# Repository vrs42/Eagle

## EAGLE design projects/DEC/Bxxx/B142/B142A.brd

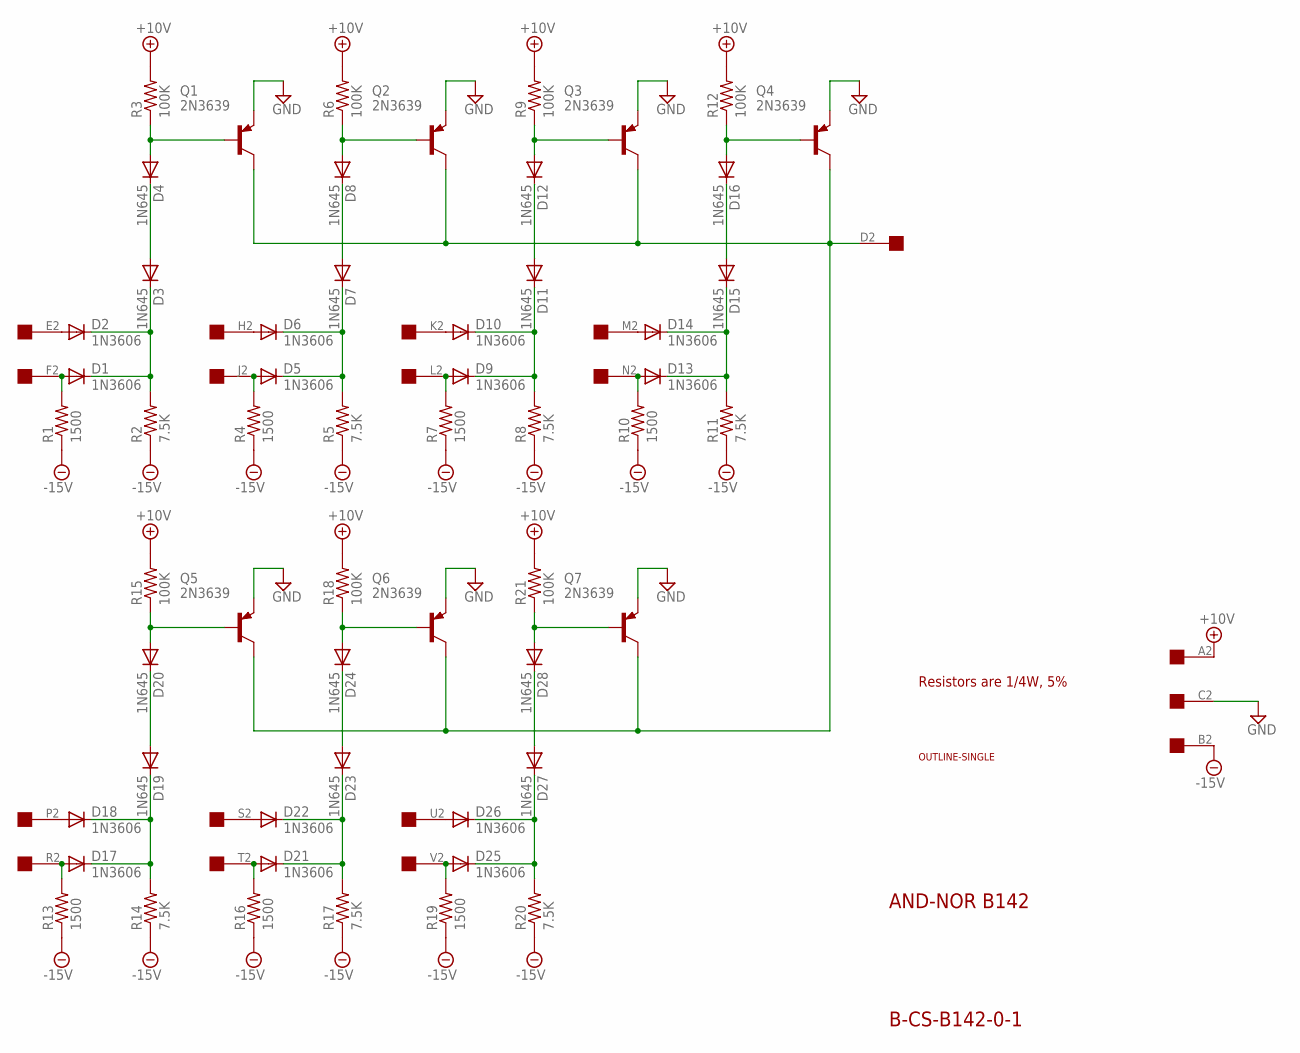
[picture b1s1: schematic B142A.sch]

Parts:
D1, D2, D5, D6, D9, D10, D13, D14, D17, D18, D21, D22, D25, D26: 1N3606; DO35-10
D3, D4, D7, D8, D11, D12, D15, D16, D19, D20, D23, D24, D27, D28: 1N645; DO35-10
Q1, Q2, Q3, Q4, Q5, Q6, Q7: 2N3639; TO39
R1, R4, R7, R10, R13, R16, R19: 1500; 0207/10
R2, R5, R8, R11, R14, R17, R20: 7.5K; 0207/10
R3, R6, R9, R12, R15, R18, R21: 100K; 0207/10
U$1: OUTLINE-SINGLE; SINGLE
U$2: EDGE-1; EDGE-CON1

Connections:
+10V: R3.2, R6.2, R9.2, R12.2, R15.2, R18.2, R21.2, U$2.A2
-15V: R1.1, R2.1, R4.1, R5.1, R7.1, R8.1, R10.1, R11.1, R13.1, R14.1, R16.1, R17.1, R19.1, R20.1, U$2.B2
GND: Q1.1 (E), Q2.1 (E), Q3.1 (E), Q4.1 (E), Q5.1 (E), Q6.1 (E), Q7.1 (E), U$2.C2
unnamed: D22.A, U$2.S2
unnamed: D4.A, Q1.2 (B), R3.1
unnamed: D3.A, D4.C
unnamed: Q1.3 (C), Q2.3 (C), Q3.3 (C), Q4.3 (C), Q5.3 (C), Q6.3 (C), Q7.3 (C), U$2.D2
unnamed: D5.A, R4.2, U$2.J2
unnamed: D12.A, Q3.2 (B), R9.1
unnamed: D10.A, U$2.K2
unnamed: D26.A, U$2.U2
unnamed: D14.A, U$2.M2
unnamed: D9.A, R7.2, U$2.L2
unnamed: D8.A, Q2.2 (B), R6.1
unnamed: D18.A, U$2.P2
unnamed: D11.A, D12.C
unnamed: D25.A, R19.2, U$2.V2
unnamed: D16.A, Q4.2 (B), R12.1
unnamed: D25.C, D26.C, D27.C, R20.2
unnamed: D15.A, D16.C
unnamed: D1.C, D2.C, D3.C, R2.2
unnamed: D5.C, D6.C, D7.C, R5.2
unnamed: D2.A, U$2.E2
unnamed: D1.A, R1.2, U$2.F2
unnamed: D7.A, D8.C
unnamed: D6.A, U$2.H2
unnamed: D13.C, D14.C, D15.C, R11.2
unnamed: D17.C, D18.C, D19.C, R14.2
unnamed: D13.A, R10.2, U$2.N2
unnamed: D20.A, Q5.2 (B), R15.1
unnamed: D21.C, D22.C, D23.C, R17.2
unnamed: D9.C, D10.C, D11.C, R8.2
unnamed: D17.A, R13.2, U$2.R2
unnamed: D19.A, D20.C
unnamed: D24.A, Q6.2 (B), R18.1
unnamed: D23.A, D24.C
unnamed: D28.A, Q7.2 (B), R21.1
unnamed: D21.A, R16.2, U$2.T2
unnamed: D27.A, D28.C

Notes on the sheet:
AND-NOR B142
B-CS-B142-0-1
Resistors are 1/4W, 5%

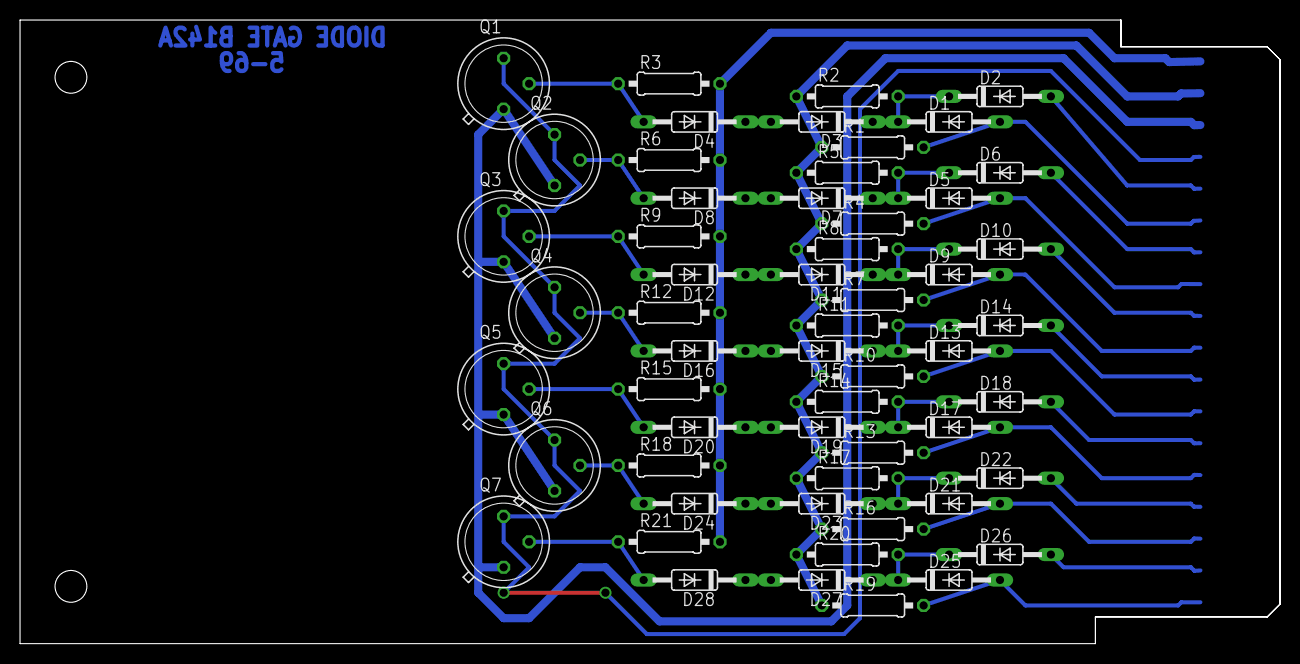
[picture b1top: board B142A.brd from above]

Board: 2 copper layers, 125.7 x 62.2 mm, 58 parts (0 on the bottom side), 39 nets.

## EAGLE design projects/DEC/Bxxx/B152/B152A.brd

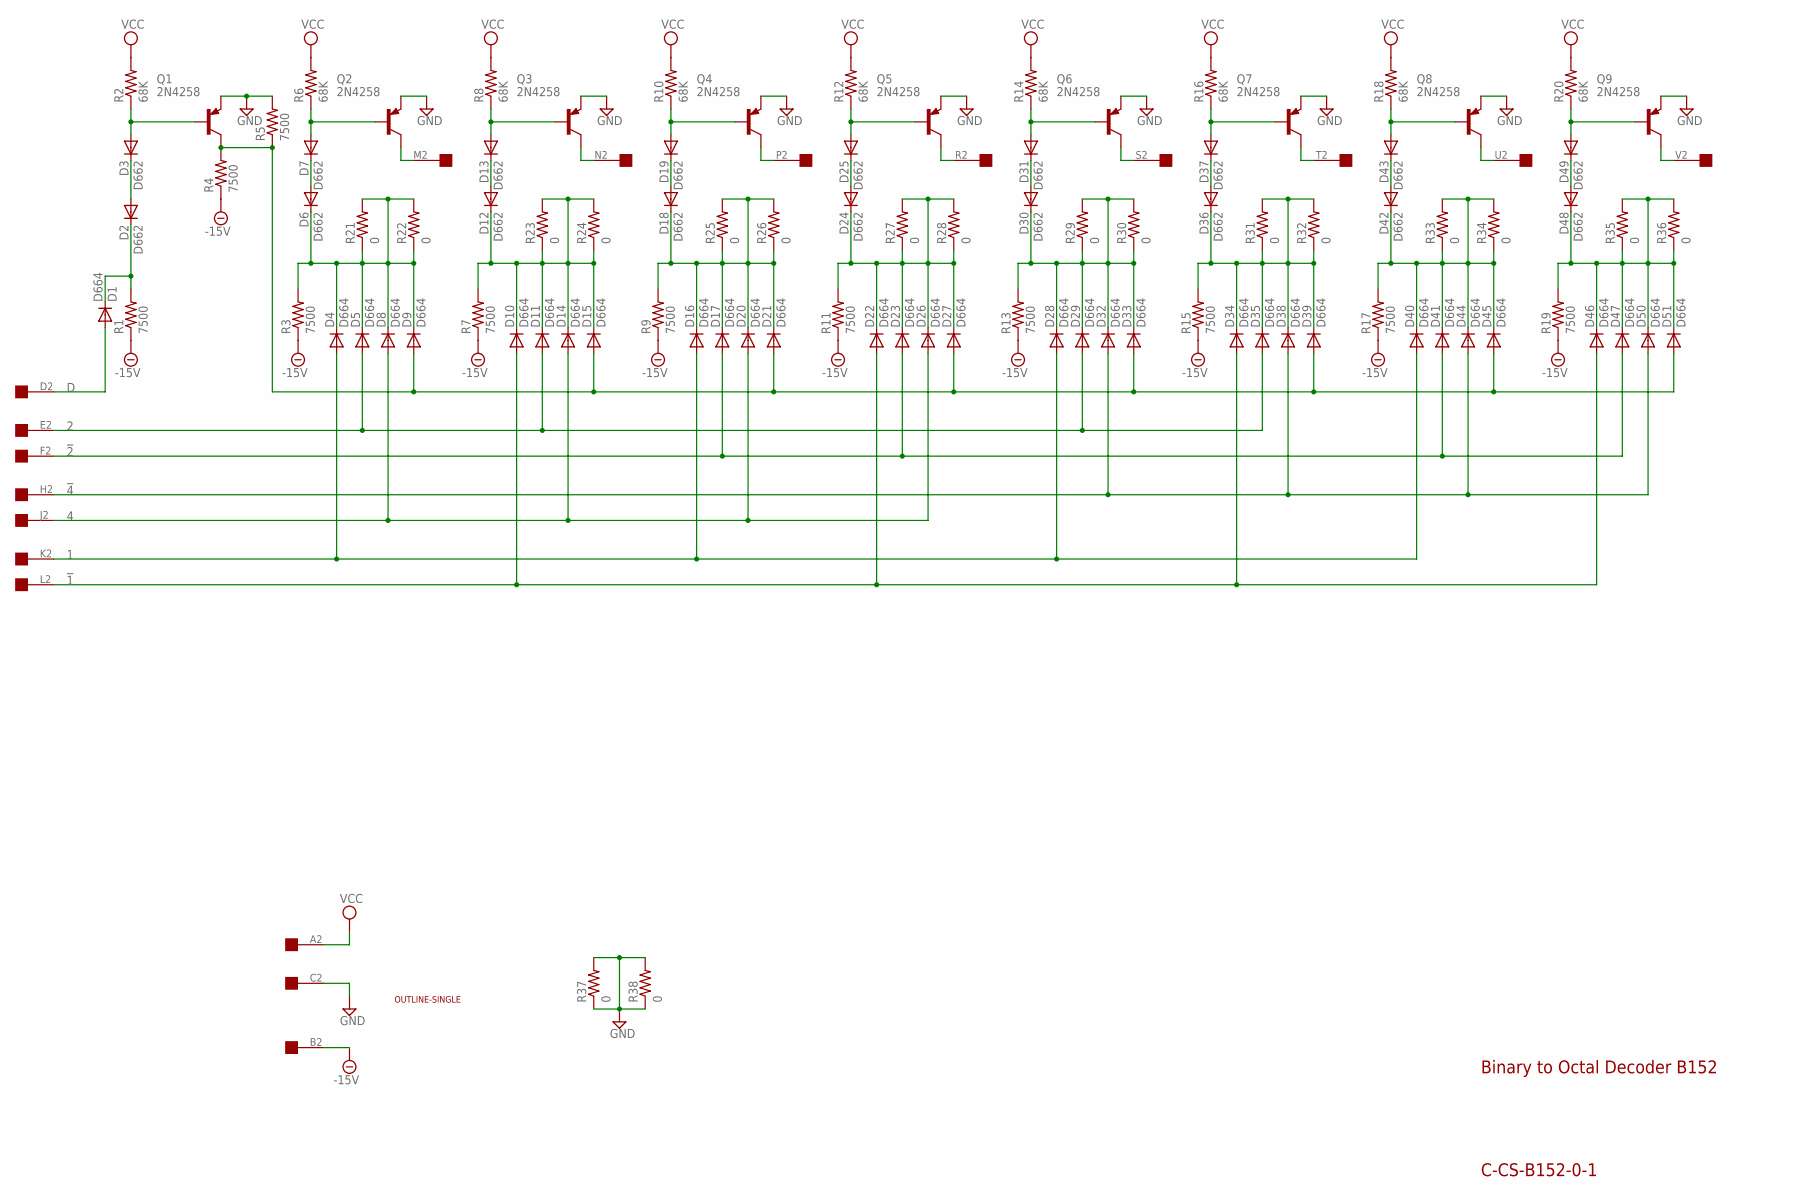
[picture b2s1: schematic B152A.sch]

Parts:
D1, D4, D5, D8, D9, D10, D11, D14, D15, D16, D17, D20, D21, D22, D23, D26, D27, D28, D29, D32, D33, D34, D35, D38, D39, D40, D41, D44, D45, D46, D47, D50, D51: D664; DO35-10
D2, D3, D6, D7, D12, D13, D18, D19, D24, D25, D30, D31, D36, D37, D42, D43, D48, D49: D662; DO35-10
Q1, Q2, Q3, Q4, Q5, Q6, Q7, Q8, Q9: 2N4258; TO5
R1, R3, R4, R5, R7, R9, R11, R13, R15, R17, R19: 7500; 0207/10
R2, R6, R8, R10, R12, R14, R16, R18, R20: 68K; 0207/10
R21, R22, R23, R24, R25, R26, R27, R28, R29, R30, R31, R32, R33, R34, R35, R36, R37, R38: 0; 0207/10
U$1: OUTLINE-SINGLE; SINGLE
U$2: EDGE-1; EDGE-CON1

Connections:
1: D4.A, D16.A, D28.A, D40.A, U$2.K2
2: D5.A, D11.A, D29.A, D35.A, U$2.E2
4: D8.A, D14.A, D20.A, D26.A, U$2.J2
!1: D10.A, D22.A, D34.A, D46.A, U$2.L2
!2: D17.A, D23.A, D41.A, D47.A, U$2.F2
!4: D32.A, D38.A, D44.A, D50.A, U$2.H2
-15V: R1.1, R3.1, R4.1, R7.1, R9.1, R11.1, R13.1, R15.1, R17.1, R19.1, U$2.B2
D: D1.A, U$2.D2
GND: Q1.1 (E), Q2.1 (E), Q3.1 (E), Q4.1 (E), Q5.1 (E), Q6.1 (E), Q7.1 (E), Q8.1 (E), Q9.1 (E), R5.2, R37.1, R37.2, R38.1, R38.2, U$2.C2
unnamed: D3.A, Q1.2 (B), R2.1
unnamed: D2.A, D3.C
unnamed: D1.C, D2.C, R1.2
unnamed: D9.A, D15.A, D21.A, D27.A, D33.A, D39.A, D45.A, D51.A, Q1.3 (C), R4.2, R5.1
unnamed: D28.C, D29.C, D30.C, D32.C, D33.C, R13.2, R29.1, R29.2, R30.1, R30.2
unnamed: D34.C, D35.C, D36.C, D38.C, D39.C, R15.2, R31.1, R31.2, R32.1, R32.2
unnamed: D40.C, D41.C, D42.C, D44.C, D45.C, R17.2, R33.1, R33.2, R34.1, R34.2
unnamed: D46.C, D47.C, D48.C, D50.C, D51.C, R19.2, R35.1, R35.2, R36.1, R36.2
unnamed: D4.C, D5.C, D6.C, D8.C, D9.C, R3.2, R21.1, R21.2, R22.1, R22.2
unnamed: D10.C, D11.C, D12.C, D14.C, D15.C, R7.2, R23.1, R23.2, R24.1, R24.2
unnamed: D6.A, D7.C
unnamed: D7.A, Q2.2 (B), R6.1
unnamed: Q2.3 (C), U$2.M2
unnamed: D16.C, D17.C, D18.C, D20.C, D21.C, R9.2, R25.1, R25.2, R26.1, R26.2
unnamed: D12.A, D13.C
unnamed: D13.A, Q3.2 (B), R8.1
unnamed: Q3.3 (C), U$2.N2
unnamed: D22.C, D23.C, D24.C, D26.C, D27.C, R11.2, R27.1, R27.2, R28.1, R28.2
unnamed: D18.A, D19.C
unnamed: D19.A, Q4.2 (B), R10.1
unnamed: Q4.3 (C), U$2.P2
unnamed: D24.A, D25.C
unnamed: D25.A, Q5.2 (B), R12.1
unnamed: Q5.3 (C), U$2.R2
unnamed: D30.A, D31.C
unnamed: D31.A, Q6.2 (B), R14.1
unnamed: Q6.3 (C), U$2.S2
unnamed: D36.A, D37.C
unnamed: D37.A, Q7.2 (B), R16.1
unnamed: Q7.3 (C), U$2.T2
unnamed: D42.A, D43.C
unnamed: D43.A, Q8.2 (B), R18.1
unnamed: Q8.3 (C), U$2.U2
unnamed: D48.A, D49.C
unnamed: D49.A, Q9.2 (B), R20.1
unnamed: Q9.3 (C), U$2.V2
VCC: R2.2, R6.2, R8.2, R10.2, R12.2, R14.2, R16.2, R18.2, R20.2, U$2.A2

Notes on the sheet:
Binary to Octal Decoder B152
C-CS-B152-0-1

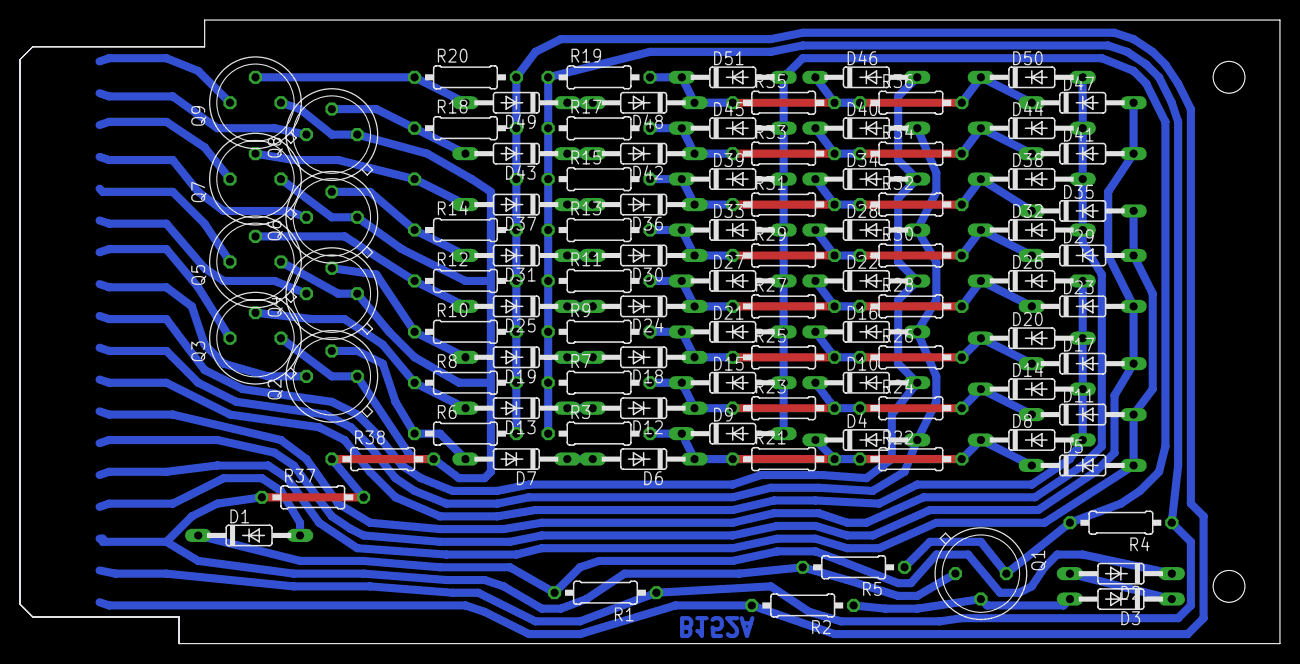
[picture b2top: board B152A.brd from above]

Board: 2 copper layers, 125.7 x 62.2 mm, 100 parts (1 on the bottom side), 46 nets.

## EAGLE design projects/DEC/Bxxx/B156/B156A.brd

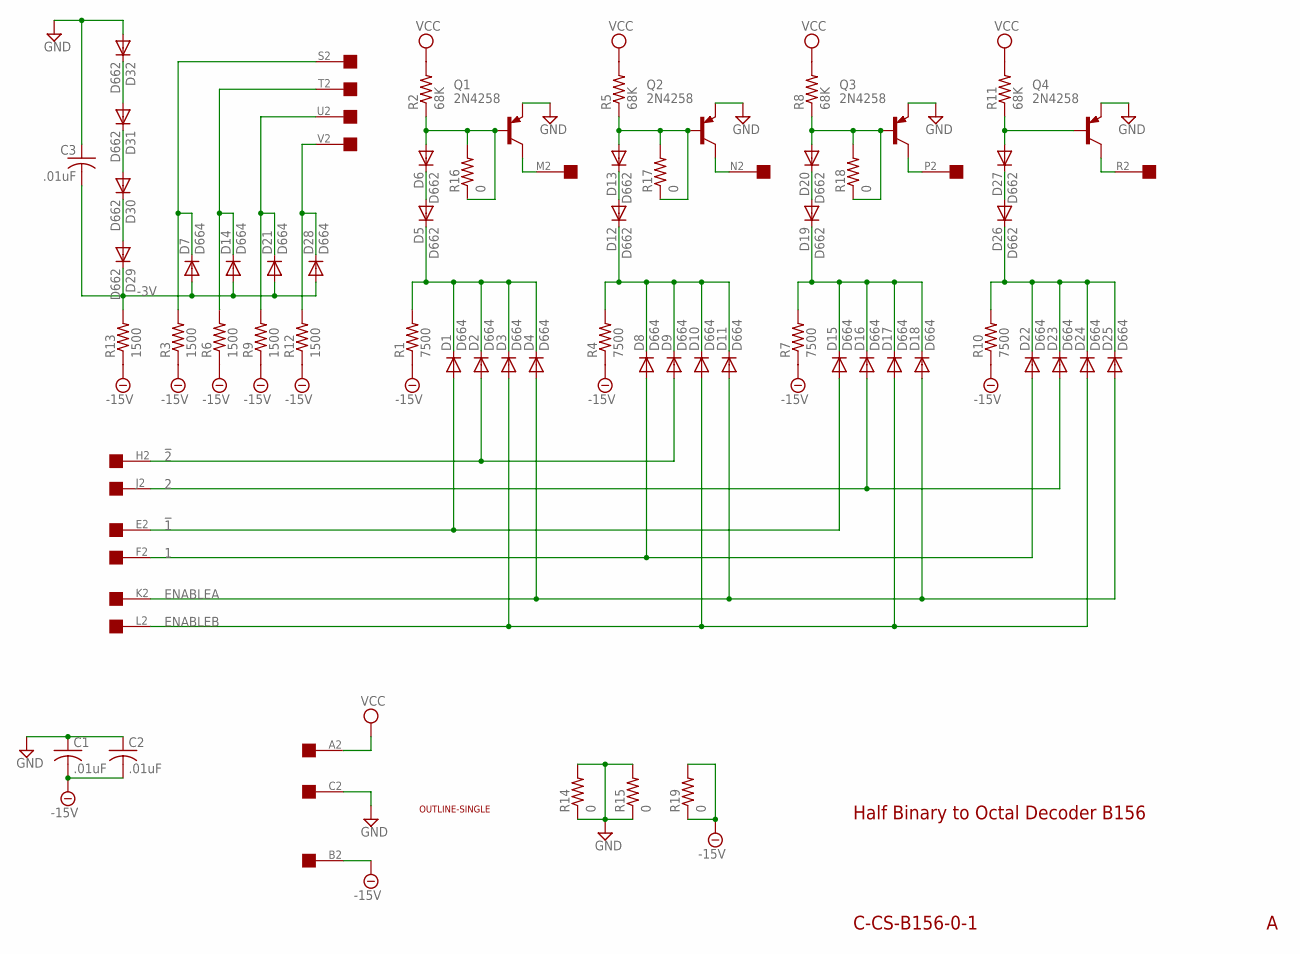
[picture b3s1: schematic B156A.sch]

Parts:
C1, C2, C3: .01uF; C063-025X075
D1, D2, D3, D4, D7, D8, D9, D10, D11, D14, D15, D16, D17, D18, D21, D22, D23, D24, D25, D28: D664; DO35-10
D5, D6, D12, D13, D19, D20, D26, D27, D29, D30, D31, D32: D662; DO35-10
Q1, Q2, Q3, Q4: 2N4258; TO5
R1, R4, R7, R10: 7500; 0207/10
R2, R5, R8, R11: 68K; 0207/10
R3, R6, R9, R12, R13: 1500; 0207/10
R14, R15, R16, R17, R18, R19: 0; 0207/10
U$1: OUTLINE-SINGLE; SINGLE
U$2: EDGE-1; EDGE-CON1

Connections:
1: D8.A, D22.A, U$2.F2
2: D16.A, D23.A, U$2.J2
!1: D1.A, D15.A, U$2.E2
!2: D2.A, D9.A, U$2.H2
-3V: C3.2, D7.A, D14.A, D21.A, D28.A, D29.C, R13.2
-15V: C1.2, C2.2, R1.1, R3.1, R4.1, R6.1, R7.1, R9.1, R10.1, R12.1, R13.1, R19.1, R19.2, U$2.B2
ENABLEA: D4.A, D11.A, D18.A, D25.A, U$2.K2
ENABLEB: D3.A, D10.A, D17.A, D24.A, U$2.L2
GND: C1.1, C2.1, C3.1, D32.A, Q1.1 (E), Q2.1 (E), Q3.1 (E), Q4.1 (E), R14.1, R14.2, R15.1, R15.2, U$2.C2
unnamed: D31.A, D32.C
unnamed: D29.A, D30.C
unnamed: D7.C, R3.2, U$2.S2
unnamed: D30.A, D31.C
unnamed: D14.C, R6.2, U$2.T2
unnamed: D21.C, R9.2, U$2.U2
unnamed: D28.C, R12.2, U$2.V2
unnamed: D1.C, D2.C, D3.C, D4.C, D5.C, R1.2
unnamed: D8.C, D9.C, D10.C, D11.C, D12.C, R4.2
unnamed: D5.A, D6.C
unnamed: D6.A, Q1.2 (B), R2.1, R16.1, R16.2
unnamed: Q1.3 (C), U$2.M2
unnamed: D15.C, D16.C, D17.C, D18.C, D19.C, R7.2
unnamed: D12.A, D13.C
unnamed: D13.A, Q2.2 (B), R5.1, R17.1, R17.2
unnamed: Q2.3 (C), U$2.N2
unnamed: D22.C, D23.C, D24.C, D25.C, D26.C, R10.2
unnamed: D19.A, D20.C
unnamed: D20.A, Q3.2 (B), R8.1, R18.1, R18.2
unnamed: Q3.3 (C), U$2.P2
unnamed: D26.A, D27.C
unnamed: D27.A, Q4.2 (B), R11.1
unnamed: Q4.3 (C), U$2.R2
VCC: R2.2, R5.2, R8.2, R11.2, U$2.A2

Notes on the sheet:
Half Binary to Octal Decoder B156
C-CS-B156-0-1

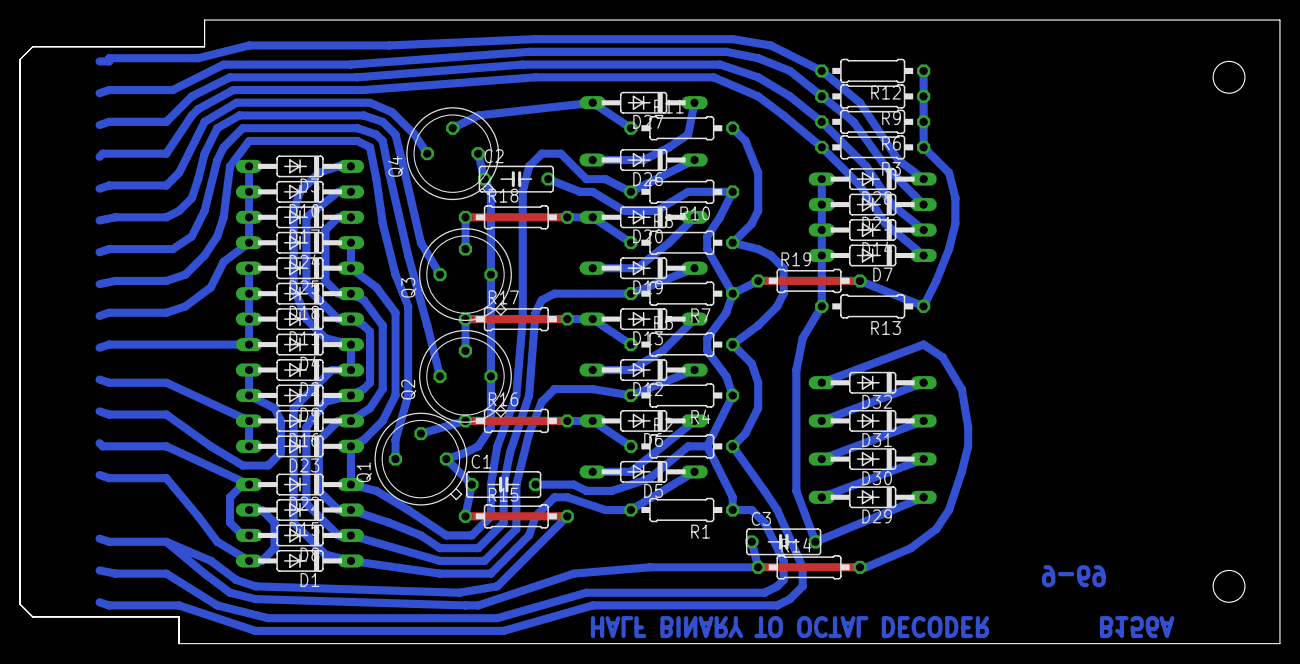
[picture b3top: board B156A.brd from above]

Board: 2 copper layers, 125.7 x 62.2 mm, 60 parts (0 on the bottom side), 33 nets.

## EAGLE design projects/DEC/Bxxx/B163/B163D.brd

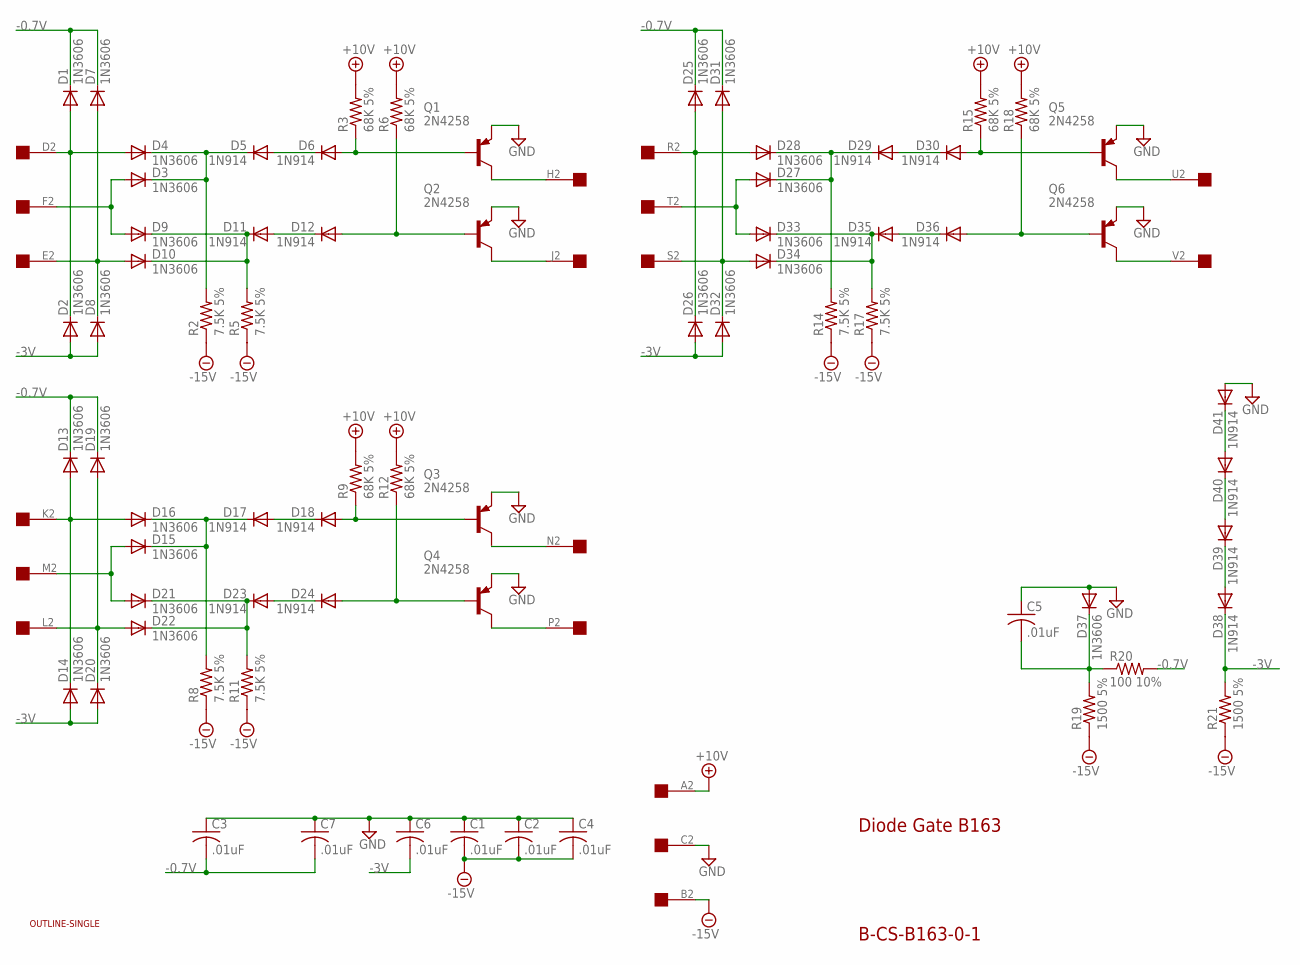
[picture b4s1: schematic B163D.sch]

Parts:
C1, C2, C3, C4, C5, C6, C7: .01uF; C050-025X075
D1, D2, D3, D4, D7, D8, D9, D10, D13, D14, D15, D16, D19, D20, D21, D22, D25, D26, D27, D28, D31, D32, D33, D34, D37: 1N3606; DO35-10
D5, D6, D11, D12, D17, D18, D23, D24, D29, D30, D35, D36, D38, D39, D40, D41: 1N914; DO35-10
Q1, Q2, Q3, Q4, Q5, Q6: 2N4258; TO39
R2, R5, R8, R11, R14, R17: 7.5K 5%; 0207/10
R3, R6, R9, R12, R15, R18: 68K 5%; 0207/10
R19, R21: 1500 5%; 0207/10
R20: 100 10%; 0207/10
U$1: OUTLINE-SINGLE; SINGLE
U$2: EDGE-1; EDGE-CON1

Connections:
+10V: R3.2, R6.2, R9.2, R12.2, R15.2, R18.2, U$2.A2
-0.7V: C3.2, C7.2, D1.C, D7.C, D13.C, D19.C, D25.C, D31.C, R20.2
-3V: C6.2, D2.A, D8.A, D14.A, D20.A, D26.A, D32.A, D38.C, R21.2
-15V: C1.2, C2.2, C4.2, R2.1, R5.1, R8.1, R11.1, R14.1, R17.1, R19.1, R21.1, U$2.B2
GND: C1.1, C2.1, C3.1, C4.1, C5.1, C6.1, C7.1, D37.A, D41.A, Q1.1 (E), Q2.1 (E), Q3.1 (E), Q4.1 (E), Q5.1 (E), Q6.1 (E), U$2.C2
unnamed: D7.A, D8.C, D10.A, U$2.E2
unnamed: D3.A, D9.A, U$2.F2
unnamed: D6.A, Q1.2 (B), R3.1
unnamed: D9.C, D10.C, D11.C, R5.2
unnamed: D3.C, D4.C, D5.C, R2.2
unnamed: D11.A, D12.C
unnamed: D12.A, Q2.2 (B), R6.1
unnamed: Q2.3 (C), U$2.J2
unnamed: D15.C, D16.C, D17.C, R8.2
unnamed: D1.A, D2.C, D4.A, U$2.D2
unnamed: Q1.3 (C), U$2.H2
unnamed: D15.A, D21.A, U$2.M2
unnamed: D13.A, D14.C, D16.A, U$2.K2
unnamed: D17.A, D18.C
unnamed: D5.A, D6.C
unnamed: D18.A, Q3.2 (B), R9.1
unnamed: Q3.3 (C), U$2.N2
unnamed: D19.A, D20.C, D22.A, U$2.L2
unnamed: D21.C, D22.C, D23.C, R11.2
unnamed: D23.A, D24.C
unnamed: D24.A, Q4.2 (B), R12.1
unnamed: Q4.3 (C), U$2.P2
unnamed: D27.C, D28.C, D29.C, R14.2
unnamed: D27.A, D33.A, U$2.T2
unnamed: D25.A, D26.C, D28.A, U$2.R2
unnamed: D40.A, D41.C
unnamed: D39.A, D40.C
unnamed: D29.A, D30.C
unnamed: D38.A, D39.C
unnamed: D30.A, Q5.2 (B), R15.1
unnamed: Q5.3 (C), U$2.U2
unnamed: D31.A, D32.C, D34.A, U$2.S2
unnamed: D33.C, D34.C, D35.C, R17.2
unnamed: D35.A, D36.C
unnamed: D36.A, Q6.2 (B), R18.1
unnamed: Q6.3 (C), U$2.V2
unnamed: C5.2, D37.C, R19.2, R20.1

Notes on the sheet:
Diode Gate B163
B-CS-B163-0-1

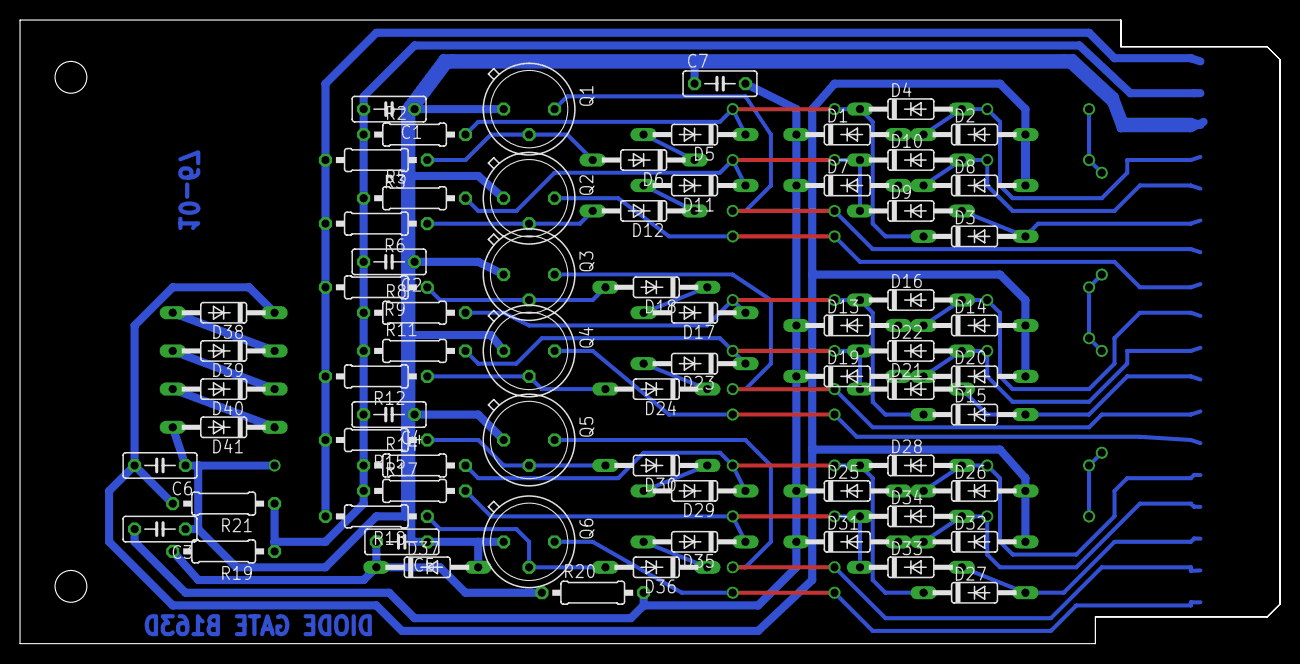
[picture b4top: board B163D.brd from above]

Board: 2 copper layers, 125.7 x 62.2 mm, 71 parts (0 on the bottom side), 42 nets.
